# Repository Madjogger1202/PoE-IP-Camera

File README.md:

# PoE-IP-Camera

**IP-камера на ESP32-CAM с питанием от PoE (с гальванической развязкой), USB или DC-Jack и STM32-буфером между Ethernet и камерой.**

Плата сетевой камеры, где полезной нагрузкой выступает модуль **ESP32-CAM**, а связку с проводной сетью обеспечивает **Ethernet-контроллер**, подключённый к **STM32**, работающей буфером/мостом. Питание выбирается из трёх источников: **PoE**, **USB** или **DC-Jack (4.2–13 В)**. PoE-вход выполнен с гальванической развязкой. На ESP32-CAM реализуются веб-функции: Telegram-бот и API.

## Обзор

- **Название проекта:** PoE-IP-Camera
- **Камера/нагрузка:** модуль ESP32-CAM (веб-сервер, Telegram-бот, API)
- **Сетевой узел:** Ethernet-контроллер + STM32 в роли буфера
- **Питание:** PoE (с развязкой) / USB / DC-Jack 4.2–13 В
- **Особенность:** изолированный PoE-вход — первый опыт проектирования гальванической развязки

## Ключевые особенности

- **Три источника питания** — PoE, USB или DC-Jack (4.2–13 В) на выбор
- **PoE с гальванической развязкой** — изолированный преобразователь питания на стороне PoE
- **ESP32-CAM как полезная нагрузка** — камера + Wi-Fi/обработка, веб-функции (Telegram-бот, API)
- **STM32-буфер** — промежуточное звено между Ethernet-контроллером и ESP32-CAM
- **Проводная сеть** — Ethernet-интерфейс для стабильного подключения и питания по одному кабелю (PoE)

## Архитектура

```
Сеть (Ethernet/PoE) ──► Ethernet-контроллер ──► STM32 (буфер) ──► ESP32-CAM (камера + веб)
                                                                       │
PoE / USB / DC-Jack ──► узел питания (PoE с развязкой) ────────────────┘
```

Сигнал из сети поступает на Ethernet-контроллер, который связан с STM32. STM32 работает буфером/мостом и передаёт данные на модуль ESP32-CAM — основную полезную нагрузку, на которой реализуются веб-интерфейс, Telegram-бот и API. Питание камера может получать по тому же кабелю (PoE) либо от USB/DC-Jack.

## Питание

Реализован выбор из трёх источников:

- **PoE** — питание по сетевому кабелю с **гальванической развязкой** (изолированный преобразователь)
- **USB** — питание от USB-разъёма
- **DC-Jack** — внешний вход **4.2–13 В**

Развязанный PoE-узел проектировался впервые и занял заметную часть работы; результат подтвердил корректность подхода.

## Что на плате

| Блок | Назначение |
|---|---|
| ESP32-CAM | Камера и веб-нагрузка (Telegram-бот, API) |
| Ethernet-контроллер | Проводной сетевой интерфейс |
| STM32 | Буфер/мост между Ethernet и ESP32-CAM |
| Узел питания PoE | Изолированный преобразователь (гальваническая развязка) |
| Выбор питания | Коммутация PoE / USB / DC-Jack (4.2–13 В) |

## Применение

- Сетевая IP-камера с питанием по одному кабелю (PoE)
- Удалённое наблюдение с управлением через Telegram-бот / API
- Узел видеомониторинга для систем с проводной сетью
- Платформа для экспериментов с PoE и связкой Ethernet ↔ ESP32-CAM

## Среда разработки

- **Схема и плата:** KiCad
- **Прошивка ESP32-CAM:** PlatformIO / Arduino (веб-сервер, Telegram-бот, API)
- **Прошивка STM32:** STM32Cube / PlatformIO

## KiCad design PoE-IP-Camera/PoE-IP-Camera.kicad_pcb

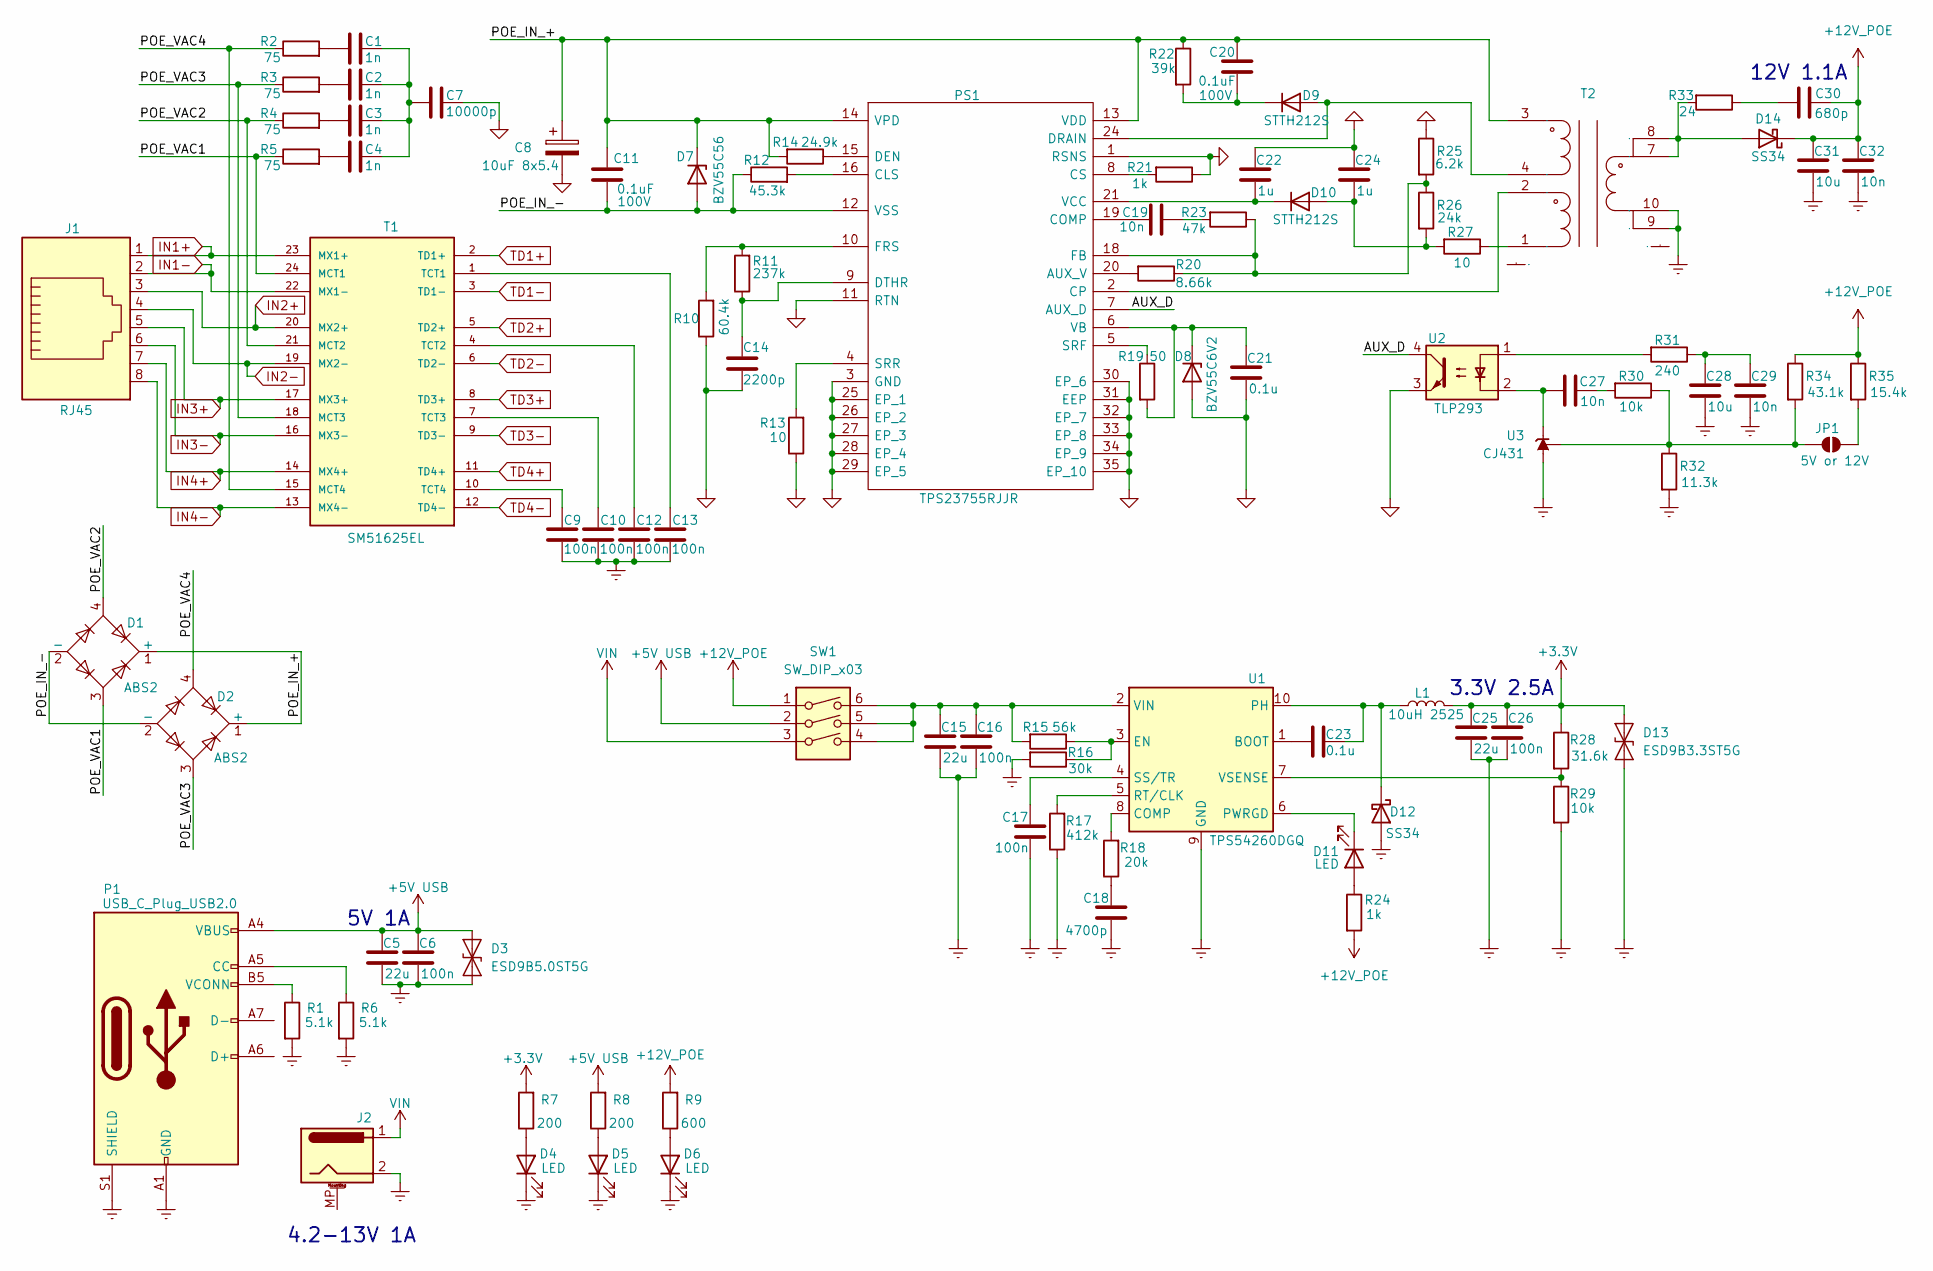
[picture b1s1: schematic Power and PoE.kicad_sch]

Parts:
C1, C2, C3, C4: 1n; C_0402_1005Metric
C5, C15, C25: 22u; C_0805_2012Metric
C6, C16, C17, C26: 100n; C_0805_2012Metric
C7: 10000p; C_0402_1005Metric
C8: 10uF 8x5.4; CP_Elec_8x5.4
C9, C10, C12, C13: 100n; C_0402_1005Metric
C11, C20: 0.1uF; C_0805_2012Metric
C14: 2200p; C_0805_2012Metric
C18: 4700p; C_0805_2012Metric
C19, C27, C29, C32: 10n; C_0805_2012Metric
C21, C23: 0.1u; C_0805_2012Metric
C22, C24: 1u; C_0805_2012Metric
C28, C31: 10u; C_0805_2012Metric
C30: 680p; C_0805_2012Metric
D1, D2: ABS2; Diode_Bridge_Diotec_ABS
D3: ESD9B5.0ST5G; D_SOD-923
D4, D5, D6, D11: LED; LED_0402_1005Metric
D7: BZV55C56; D_MiniMELF
D8: BZV55C6V2; D_MiniMELF
D9, D10: STTH212S; D_SMC
D12, D14: SS34; D_SMA
D13: ESD9B3.3ST5G; D_SOD-923
J1: RJ45; RJ45_Amphenol_54602-x08_Horizontal
J2: Barrel_Jack_MountingPin; BarrelJack_GCT_DCJ200-10-A_Horizontal
JP1: SolderJumper_2_Open; SolderJumper-2_P1.3mm_Open_RoundedPad1.0x1.5mm
L1: 10uH 2525; L_Vishay_IHLP-2525
P1: USB_C_Plug_USB2.0; USB_C_Receptacle_G-Switch_GT-USB-7010ASV
PS1: TPS23755RJJR
R1, R6: 5.1k; R_0402_1005Metric
R2, R3, R4, R5: 75; R_0402_1005Metric
R7, R8: 200; R_0402_1005Metric
R9: 600; R_0402_1005Metric
R10: 60.4k; R_0402_1005Metric
R11: 237k; R_0402_1005Metric
R12: 45.3k; R_0402_1005Metric
R13, R27: 10; R_0402_1005Metric
R14: 24.9k; R_0402_1005Metric
R15: 56k; R_0402_1005Metric
R16: 30k; R_0402_1005Metric
R17: 412k; R_0402_1005Metric
R18: 20k; R_0402_1005Metric
R19: 50; R_0402_1005Metric
R20: 8.66k; R_0402_1005Metric
R21, R24: 1k; R_0402_1005Metric
R22: 39k; R_0402_1005Metric
R23: 47k; R_0402_1005Metric
R25: 6.2k; R_0402_1005Metric
R26: 24k; R_0402_1005Metric
R28: 31.6k; R_0402_1005Metric
R29, R30: 10k; R_0402_1005Metric
R31: 240; R_0402_1005Metric
R32: 11.3k; R_0402_1005Metric
R33: 24; R_1206_3216Metric
R34: 43.1k; R_0402_1005Metric
R35: 15.4k; R_0402_1005Metric
SW1: SW_DIP_x03; SW_DIP_SPSTx03_Slide_9.78x9.8mm_W7.62mm_P2.54mm
T1: SM51625EL; XFMR_SM51625EL
T2: XFMR-SMD_HR051142; Manufacturer Part HR051142
U1: TPS54260DGQ; MSOP-10-1EP_3x3mm_P0.5mm_EP2.2x3.1mm_Mask1.83x1.89mm_Therma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
U2: TLP293; SOIC-4_4.55x2.6mm_P1.27mm
U3: CJ431; SOT-23

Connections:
+3.3V: C25.1, C26.1, D13.2 (A2), L1.2, R7.2, R28.1; also elsewhere on the board
+5V USB: C5.1, C6.1, D3.2 (A2), P1.A4 (VBUS), P1.A9 (VBUS), P1.B4 (VBUS), P1.B9 (VBUS), R8.2, SW1.2
+12V_POE: C30.2, C31.1, C32.1, D14.1 (K), R9.2, R24.2, R34.1, R35.1, SW1.1
/Power and PoE/AUX_D: PS1.7 (AUX_D), U2.4
/Power and PoE/POE_IN_+: C8.1, C11.1, C20.1, D1.1 (+), D2.1 (+), D7.1 (K), PS1.13 (VDD), PS1.14 (VPD), R14.2, R22.1, T2.3
/Power and PoE/POE_IN_-: C11.2, D1.2 (-), D2.2 (-), D7.2 (A), PS1.12 (VSS), R12.1
/Power and PoE/POE_VAC1: D1.3, R5.1, T1.24 (MCT1)
/Power and PoE/POE_VAC2: D1.4, R4.1, T1.21 (MCT2)
/Power and PoE/POE_VAC3: D2.3, R3.1, T1.18 (MCT3)
/Power and PoE/POE_VAC4: D2.4, R2.1, T1.15 (MCT4)
Earth: C5.2, C6.2, C9.1, C10.1, C12.1, C13.1, C15.2, C16.2, C17.2, C18.2, C25.2, C26.2, C28.2, C29.2, C31.2, C32.2, D3.1 (A1), D4.1 (K), D5.1 (K), D6.1 (K), D12.2 (A), D13.1 (A1), J2.2, P1.A1 (GND), P1.A12 (GND), P1.B1 (GND), P1.B12 (GND), P1.S1 (SHIELD), R1.2, R6.2, R16.2, R17.1, R29.2, R32.2, T2.9, T2.10, U1.9 (GND), U1.11, U3.3 (A); also elsewhere on the board
GND1: C7.1, C8.2, C14.2, C21.2, C22.1, C24.1, D8.2 (A), PS1.1 (RSNS), PS1.3 (GND), PS1.11 (RTN), PS1.25 (EP_1), PS1.26 (EP_2), PS1.27 (EP_3), PS1.28 (EP_4), PS1.29 (EP_5), PS1.30 (EP_6), PS1.31 (EEP), PS1.32 (EP_7), PS1.33 (EP_8), PS1.34 (EP_9), PS1.35 (EP_10), R10.1, R13.1, R21.1, R25.1, U2.3
IN1+: J1.1, T1.23 (MX1+)
IN1-: J1.2, T1.22 (MX1-)
IN2+: J1.3, T1.20 (MX2+)
IN2-: J1.4, T1.19 (MX2-)
IN3+: J1.5, T1.17 (MX3+)
IN3-: J1.6, T1.16 (MX3-)
IN4+: J1.7, T1.14 (MX4+)
IN4-: J1.8, T1.13 (MX4-)
unnamed: C1.1, C2.1, C3.1, C4.1, C7.2
unnamed: C1.2, R2.2
unnamed: C2.2, R3.2
unnamed: C3.2, R4.2
unnamed: C4.2, R5.2
unnamed: C18.1, R18.1
unnamed: C19.2, R23.2
unnamed: C27.2, R30.2
unnamed: C28.1, C29.1, R31.1
unnamed: C30.1, R33.1
unnamed: D4.2 (A), R7.1
unnamed: D5.2 (A), R8.1
unnamed: D6.2 (A), R9.1
unnamed: C21.1, D8.1 (K), PS1.6 (VB), R19.2
unnamed: D9.2 (A), PS1.24 (DRAIN), T2.4
unnamed: C20.2, D9.1 (K), R22.2
unnamed: C24.2, D10.2 (A), R26.2, R27.2
unnamed: C22.2, D10.1 (K), PS1.21 (VCC)
unnamed: D11.2 (A), R24.1
unnamed: D11.1 (K), U1.6 (PWRGD)
unnamed: C23.2, D12.1 (K), L1.1, U1.10 (PH)
unnamed: D14.2 (A), R33.2, T2.7, T2.8
unnamed: JP1.1 (A), R30.1, R32.1, R34.2, U3.1 (REF)
unnamed: JP1.2 (B), R35.2
unnamed: P1.A5 (CC), R6.1
unnamed: P1.B5 (VCONN), R1.1
unnamed: PS1.20 (AUX_V), R20.2
unnamed: PS1.16 (CLS), R12.2
unnamed: C19.1, PS1.19 (COMP)
unnamed: PS1.2 (CP), T2.2
unnamed: PS1.8 (CS), R21.2
unnamed: PS1.15 (DEN), R14.1
unnamed: C14.1, PS1.9 (DTHR), R11.1
unnamed: PS1.18 (FB), R20.1, R23.1, R25.2, R26.1
unnamed: PS1.10 (FRS), R10.2, R11.2
unnamed: PS1.5 (SRF), R19.1
unnamed: PS1.4 (SRR), R13.2
unnamed: R27.1, T2.1
unnamed: R31.2, U2.1
unnamed: C13.2, T1.1 (TCT1)
unnamed: C12.2, T1.4 (TCT2)
unnamed: C10.2, T1.7 (TCT3)
unnamed: C9.2, T1.10 (TCT4)
unnamed: C23.1, U1.1 (BOOT)
unnamed: R18.2, U1.8 (COMP)
unnamed: R15.1, R16.1, U1.3 (EN)
unnamed: R17.2, U1.5 (RT/CLK)
unnamed: C17.1, U1.4 (SS/TR)
unnamed: C15.1, C16.1, R15.2, SW1.4, SW1.5, SW1.6, U1.2 (VIN)
unnamed: R28.2, R29.1, U1.7 (VSENSE)
unnamed: C27.1, U2.2, U3.2 (K)
TD1+: T1.2 (TD1+); also elsewhere on the board
TD1-: T1.3 (TD1-); also elsewhere on the board
TD2+: T1.5 (TD2+); also elsewhere on the board
TD2-: T1.6 (TD2-); also elsewhere on the board
TD3+: T1.8 (TD3+)
TD3-: T1.9 (TD3-)
TD4+: T1.11 (TD4+)
TD4-: T1.12 (TD4-)
VIN: J2.1, SW1.3

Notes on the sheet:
3.3V 2.5A
12V 1.1A
5V 1A
4.2-13V 1A

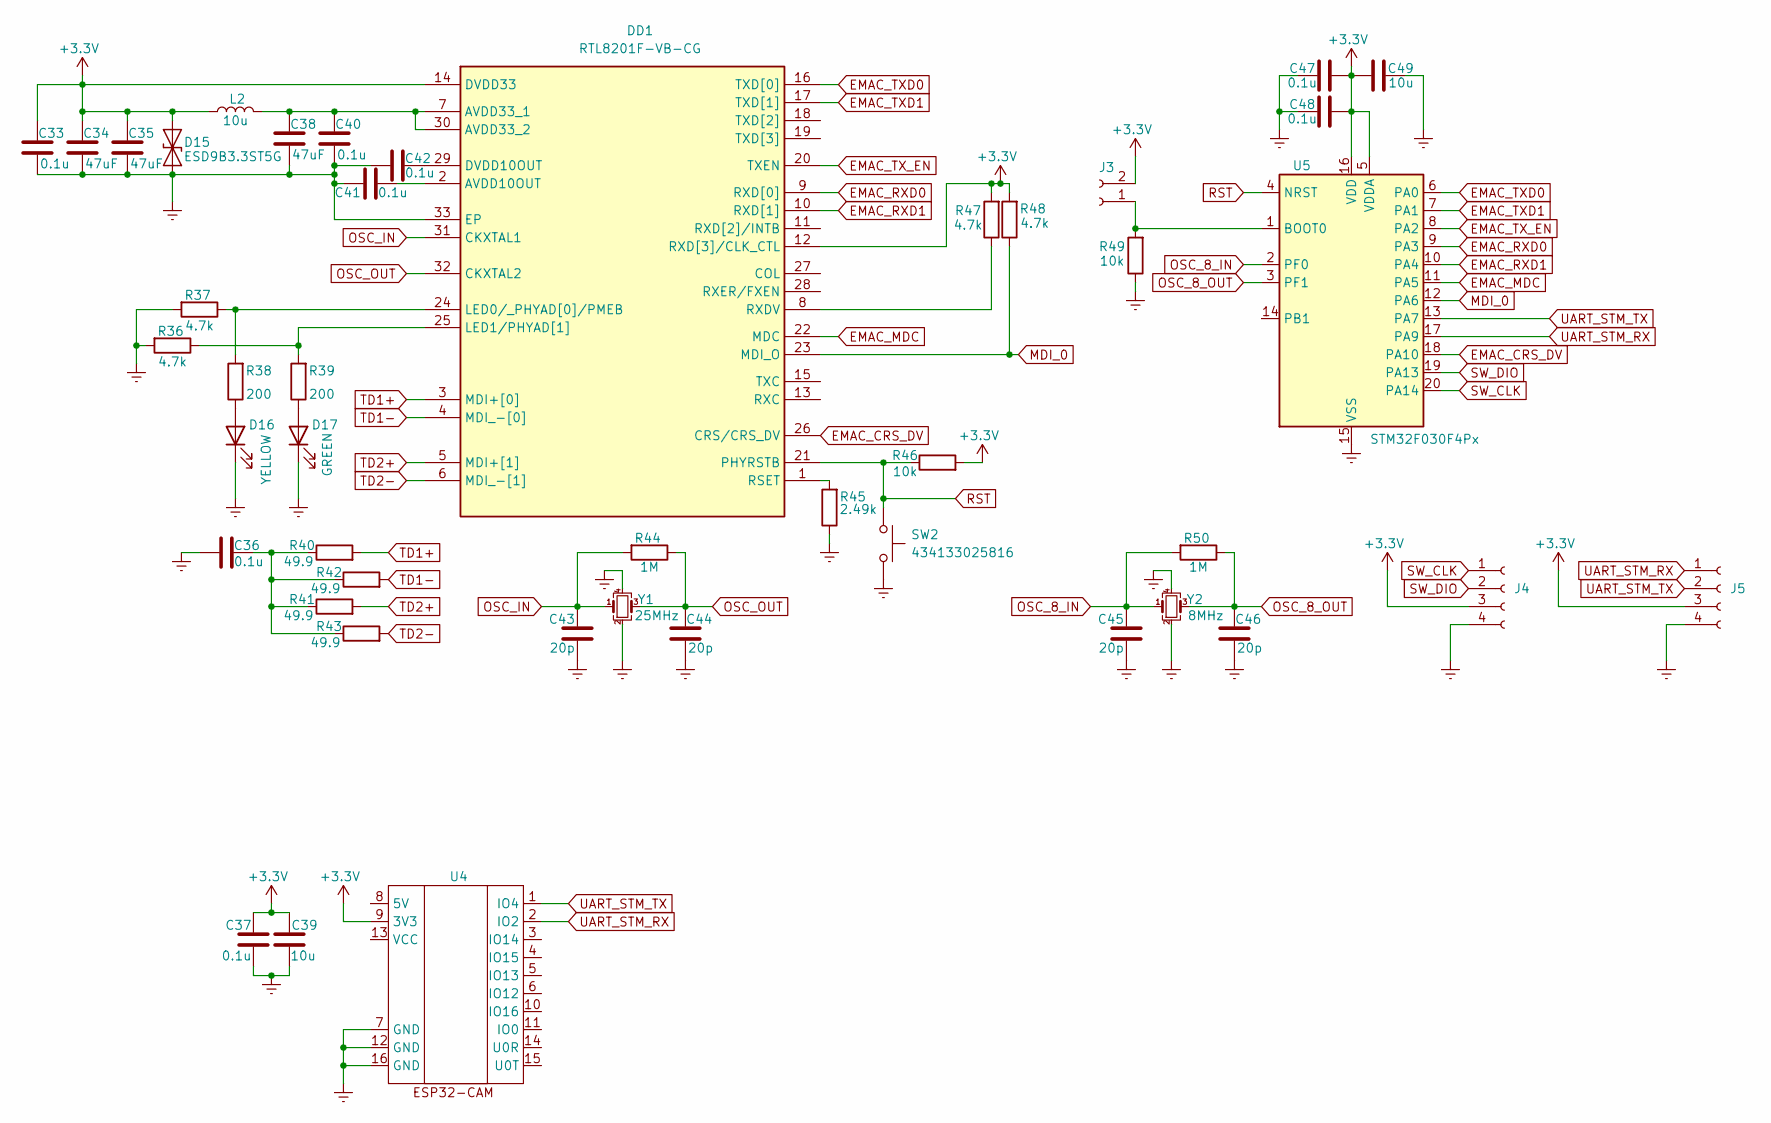
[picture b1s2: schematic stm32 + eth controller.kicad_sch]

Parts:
C33, C40, C41, C42: 0.1u; C_0805_2012Metric
C34, C35, C38: 47uF; C_0805_2012Metric
C36: 0.1u; C_0603_1608Metric
C37, C47, C48: 0.1u; C_0402_1005Metric
C39, C49: 10u; C_0402_1005Metric
C43, C44, C45, C46: 20p; C_0402_1005Metric
D15: ESD9B3.3ST5G; D_SOD-923
D16: YELLOW; LED_0402_1005Metric
D17: GREEN; LED_0402_1005Metric
DD1: RTL8201F-VB-CG; QFN50P500X500X100-33N; Manufacturer_Part_Number RTL8201F-VB-CG
J3: Conn_01x0; PinHeader_1x02_P2.54mm_Vertical
J4, J5: Conn_01x04_Socket; PinHeader_1x04_P2.54mm_Vertical
L2: 10u; L_0805_2012Metric
R36, R37, R47, R48: 4.7k; R_0402_1005Metric
R38, R39: 200; R_0402_1005Metric
R40, R41, R42, R43: 49.9; R_0402_1005Metric
R44, R50: 1M; R_0402_1005Metric
R45: 2.49k; R_0402_1005Metric
R46, R49: 10k; R_0402_1005Metric
SW2: 434133025816; SW_Push_1P1T_NO_Vertical_Wuerth_434133025816
U4: COMM-TH_16P-L40.0-W27.0-P2.54_ESP32-CAM
U5: STM32F030F4Px; TSSOP-20_4.4x6.5mm_P0.65mm
Y1, Y2: X322525MOB4SI; Oscillator_SMD_Abracon_ASE-4Pin_3.2x2.5mm

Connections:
+3.3V: C33.1, C34.1, C35.1, C37.1, C39.2, C47.1, C48.1, C49.1, D15.2 (A2), DD1.12 (RXD[3]/CLK_CTL), DD1.14 (DVDD33), J3.2, J4.3, J5.3, L2.1, R46.2, R47.2, R48.2, U4.9 (3V3), U5.5 (VDDA), U5.16 (VDD); also elsewhere on the board
EMAC_CRS_DV: DD1.26 (CRS/CRS_DV), U5.18 (PA10)
EMAC_MDC: DD1.22 (MDC), U5.11 (PA5)
EMAC_RXD0: DD1.9 (RXD[0]), U5.9 (PA3)
EMAC_RXD1: DD1.10 (RXD[1]), U5.10 (PA4)
EMAC_TXD0: DD1.16 (TXD[0]), U5.6 (PA0)
EMAC_TXD1: DD1.17 (TXD[1]), U5.7 (PA1)
EMAC_TX_EN: DD1.20 (TXEN), U5.8 (PA2)
Earth: C33.2, C34.2, C35.2, C36.1, C37.2, C38.2, C39.1, C40.2, C41.1, C42.1, C43.1, C44.2, C45.1, C46.2, C47.2, C48.2, C49.2, D15.1 (A1), D16.1 (K), D17.1 (K), DD1.33 (EP), J4.4, J5.4, R36.2, R37.2, R45.1, R49.1, SW2.2, U4.7 (GND), U4.12 (GND), U4.16 (GND), U5.15 (VSS), Y1.2, Y1.4, Y2.2, Y2.4; also elsewhere on the board
MDI_0: DD1.23 (MDI_O), R48.1, U5.12 (PA6)
unnamed: C36.2, R40.1, R41.1, R42.1, R43.1
unnamed: D16.2 (A), R38.1
unnamed: D17.2 (A), R39.1
unnamed: C41.2, DD1.2 (AVDD10OUT)
unnamed: C38.1, C40.1, DD1.7 (AVDD33_1), DD1.30 (AVDD33_2), L2.2
unnamed: C42.2, DD1.29 (DVDD10OUT)
unnamed: DD1.24 (LED0/_PHYAD[0]/PMEB), R37.1, R38.2
unnamed: DD1.25 (LED1/PHYAD[1]), R36.1, R39.2
unnamed: DD1.1 (RSET), R45.2
unnamed: DD1.8 (RXDV), R47.1
unnamed: J3.1, R49.2, U5.1 (BOOT0)
OSC_8_IN: C45.2, R50.2, U5.2 (PF0), Y2.1
OSC_8_OUT: C46.1, R50.1, U5.3 (PF1), Y2.3
OSC_IN: C43.2, DD1.31 (CKXTAL1), R44.2, Y1.1
OSC_OUT: C44.1, DD1.32 (CKXTAL2), R44.1, Y1.3
RST: DD1.21 (PHYRSTB), R46.1, SW2.1, U5.4 (NRST)
SW_CLK: J4.1, U5.20 (PA14)
SW_DIO: J4.2, U5.19 (PA13)
TD1+: DD1.3 (MDI+[0]), R40.2; also elsewhere on the board
TD1-: DD1.4 (MDI_-[0]), R42.2; also elsewhere on the board
TD2+: DD1.5 (MDI+[1]), R41.2; also elsewhere on the board
TD2-: DD1.6 (MDI_-[1]), R43.2; also elsewhere on the board
UART_STM_RX: J5.1, U4.2 (IO2), U5.17 (PA9)
UART_STM_TX: J5.2, U4.1 (IO4), U5.13 (PA7)

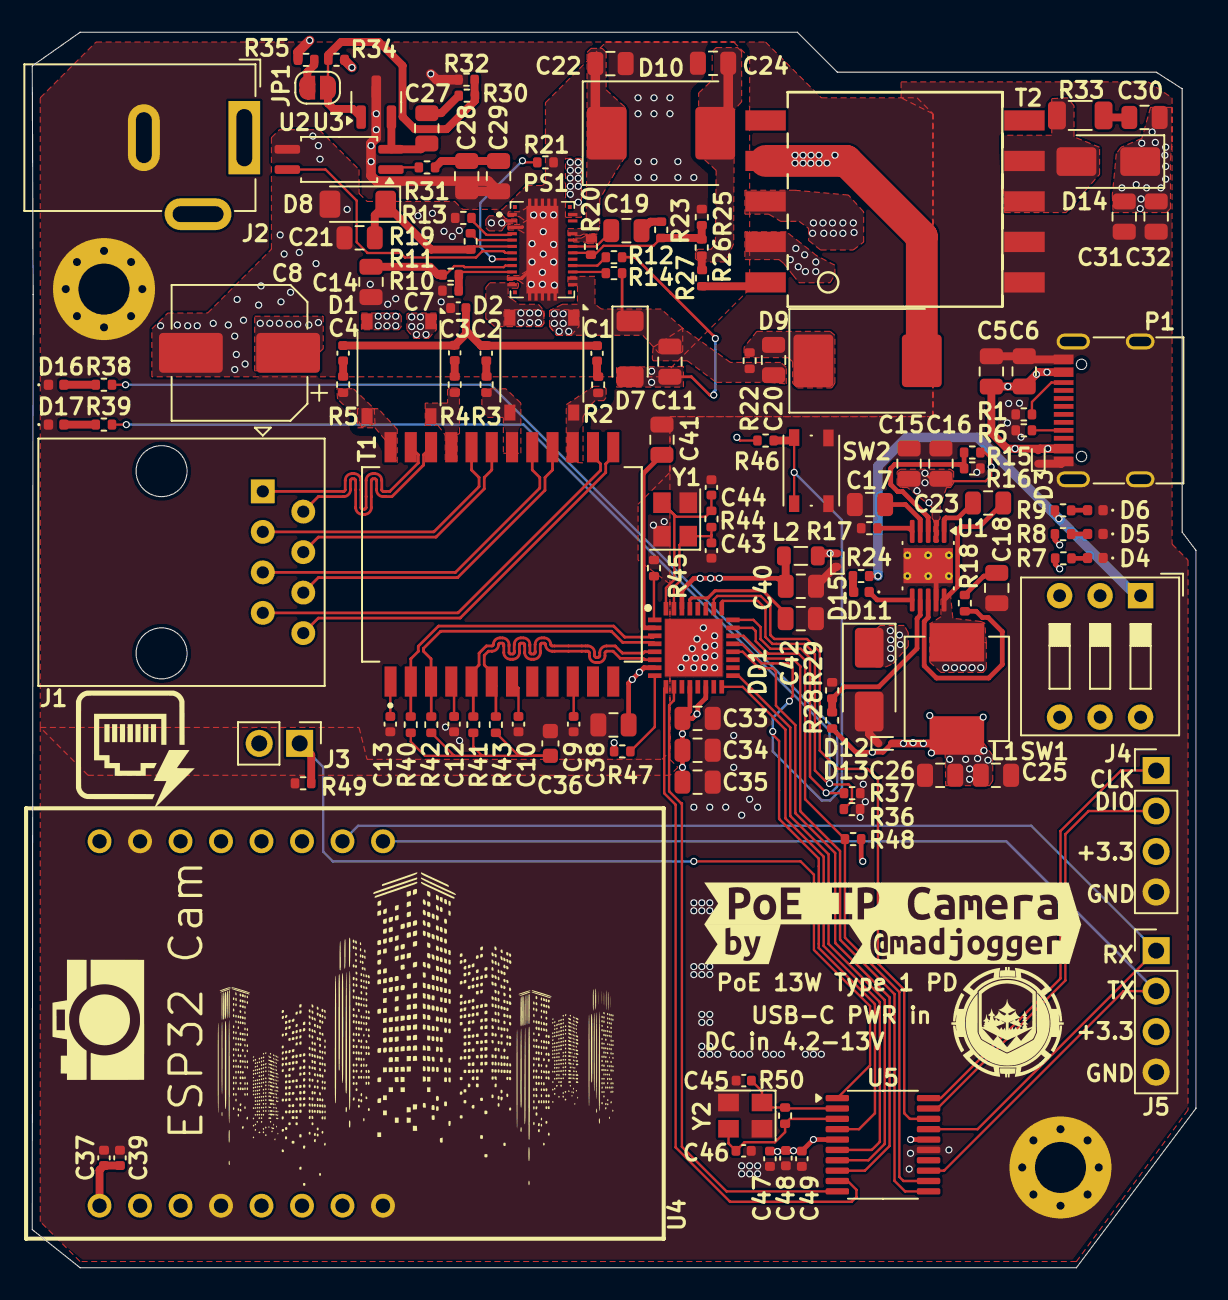
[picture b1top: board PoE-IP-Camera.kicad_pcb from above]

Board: 4 copper layers, 73.0 x 77.5 mm, 141 parts (0 on the bottom side), 104 nets.

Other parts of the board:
kibuzzard-67A49B3B: G***; kibuzzard-67A49B3B
kibuzzard-67A49B47: G***; kibuzzard-67A49B47
kibuzzard-67A498E6: G***; kibuzzard-67A498E6

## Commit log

2025-02-03 rev0 without routing
2025-02-03 частичная трассировка
2025-02-05 чут чут трассировки
2025-02-06 Завершение трассировки
